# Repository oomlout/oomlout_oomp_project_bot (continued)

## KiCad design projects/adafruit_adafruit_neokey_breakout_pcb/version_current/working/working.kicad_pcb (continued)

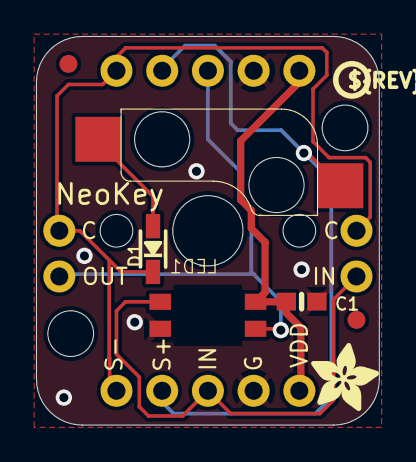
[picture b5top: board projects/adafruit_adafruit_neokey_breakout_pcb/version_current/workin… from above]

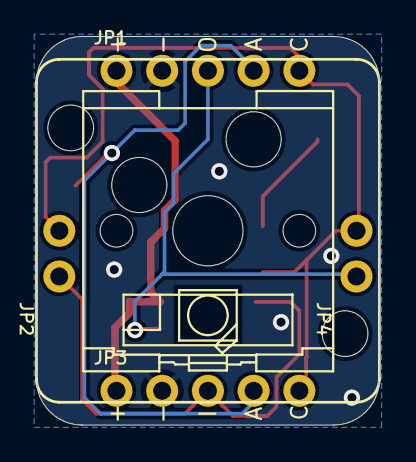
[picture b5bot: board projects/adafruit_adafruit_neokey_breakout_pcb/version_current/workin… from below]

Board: 2 copper layers, 19.1 x 21.6 mm, 14 parts (6 on the bottom side), 7 nets.

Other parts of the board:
@HOLE0, @HOLE1: (no value)
U$1: PCBFEAT-REV-040
U$2: ADAFRUIT_3.5MM

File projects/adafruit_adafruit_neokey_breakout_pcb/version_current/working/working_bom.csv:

Row,Description,Part,References,Value,Footprint,Quantity Per PCB,Status,Datasheet
1,,CAP_CERAMIC0603_NO,C1,1uF,0603-NO,1, ,
2,,DIODESOD-323,D1,1N4148,SOD-323,1, ,
3,,HEADER-1X2ROUND,JP2 JP4,HEADER-1X2ROUND,1X02_ROUND,2, ,
4,,HEADER-1X570MIL,JP1 JP3,HEADER-1X570MIL,1X05_ROUND_70,2, ,
5,,WS2812B_SK6812E,LED1,WS2812B_SK6812E,NEO3535_REVERSE,1, ,
6,,SWITCH_PUSHBUTTON_KAILH_SOCKET,SW1,SWITCH_PUSHBUTTON_KAILH_SOCKET,KAILH_SOCKET,1, ,





Project info:
Schematic:,working
Variant:,default
Revision:,
Date:,2023-08-03_17-21-22
KiCad Version:,7.0.6-7.0.6~ubuntu22.04.1
Statistics:
Component Groups:,6
Component Count:,8 (0 SMD/ 0 THT)
Fitted Components:,8 (0 SMD/ 0 THT)
Number of PCBs:,1
Total Components:,8

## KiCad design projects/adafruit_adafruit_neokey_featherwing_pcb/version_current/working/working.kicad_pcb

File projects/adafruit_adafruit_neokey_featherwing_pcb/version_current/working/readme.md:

# OOMP Project  
## Adafruit-NeoKey-FeatherWing-PCB  by adafruit  
  
oomp key: oomp_projects_flat_adafruit_adafruit_neokey_featherwing_pcb  
(snippet of original readme)  
  
-- Adafruit NeoKey FeatherWing PCB  
  
<a href="http://www.adafruit.com/products/4979"><br/>  
Click here to purchase one from the Adafruit shop</a>  
  
PCB files for the Adafruit NeoKey FeatherWing.   
  
Format is EagleCAD schematic and board layout  
* https://www.adafruit.com/product/4979  
  
--- Description  
  
The only thing better than a nice mechanical key, is two of them, and ones that also can glow any color of the rainbow - and that's what the Adafruit NeoKey FeatherWing will let you do! This Wing plugs into any/all Feather main boards and can fit two Cherry MX or compatible switches to turn your Feather into the lil'est macro keypad.  
  
Each Wing has two Kailh sockets, which means you can plug in any MX-compatible switches instead of soldering them in. You may need a little glue to keep the switches in place: hot glue or a dot of epoxy worked fine for us.  
  
Beneath each switch is a reverse-mount NeoPixel pointing up through the spot where many switches would have an LED to shine though. The two pixels are chained together so you can control them as one 2-pixel NeoPixel strand.  
  
We wired the switches up very simply, so you can use with any Feather. There's jumper pads you can cut to re-wire the switches and LED strand.  
  
* Switch A - Connects to the Feather pin to the left of SCL, on most Feathers this is pin D5  
* Switch B - Connects to the Feather pin two pins to the left of SCL, on most Feathers this is pin D6  
* NeoPixel Input - Connects  
  full source readme at [readme_src.md](readme_src.md)  
  
source repo at: [https://github.com/adafruit/Adafruit-NeoKey-FeatherWing-PCB](https://github.com/adafruit/Adafruit-NeoKey-FeatherWing-PCB)  
## Board  

## Schematic  

[schematic pdf](working_schematic.pdf)  
## Images

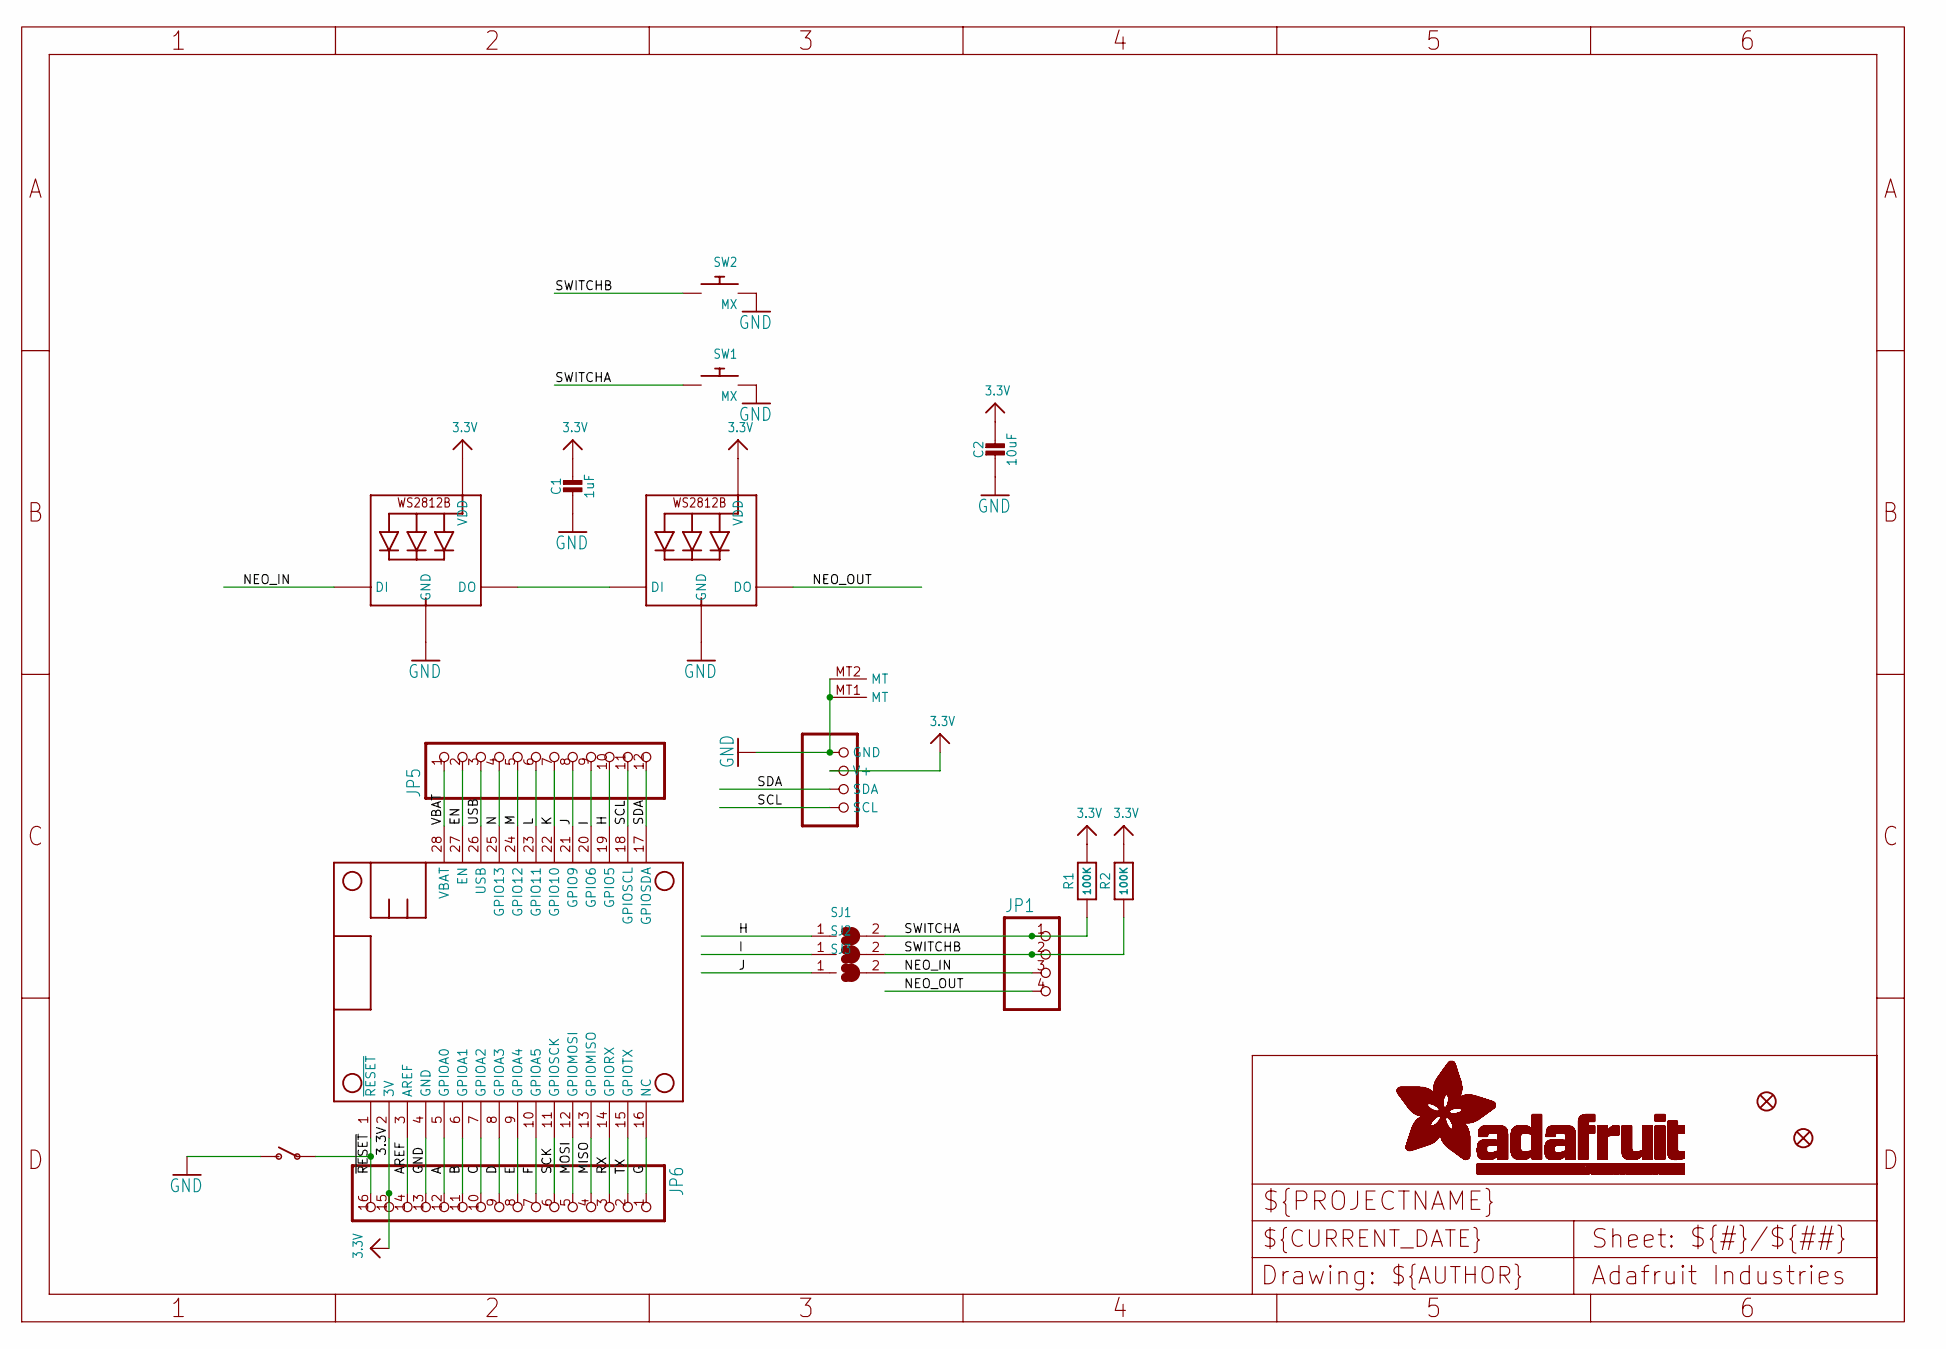
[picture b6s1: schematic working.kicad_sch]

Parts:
C1: 1uF; 0603-NO
C2: 10uF; 0805-NO
CONN1: STEMMA_I2C_QT; JST_SH4
FID1, FID2: FIDUCIAL_1MM
JP1: HEADER-1X4ROUND; 1X04_ROUND
JP5: HEADER-1X12; 1X12_ROUND
JP6: HEADER-1X16ROUND; 1X16_ROUND
LED1, LED2: WS2812B_SK6812E; NEO3535_REVERSE
MS1: FEATHERWING_NODIM
R1, R2: 100K; 0603-NO
SJ1, SJ2, SJ3: SOLDERJUMPERCLOSED; SOLDERJUMPER_CLOSEDWIRE
SW1, SW2: MX; KAILH_SOCKET
SW3: SWITCH_SPST_TACT_RA; SPST_TACTILE_RA

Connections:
3.3V: C1.1, C2.1, CONN1.2 (V+), JP6.15, LED1.1-VDD (VDD), LED2.1-VDD (VDD), MS1.2 (3V), R1.2, R2.2
A: JP6.12, MS1.5 (GPIOA0)
AREF: JP6.14, MS1.3 (AREF)
B: JP6.11, MS1.6 (GPIOA1)
C: JP6.10, MS1.7 (GPIOA2)
D: JP6.9, MS1.8 (GPIOA3)
E: JP6.8, MS1.9 (GPIOA4)
EN: JP5.2, MS1.27 (EN)
F: JP6.7, MS1.10 (GPIOA5)
G: JP6.1, MS1.16 (NC)
GND: C1.2, C2.2, CONN1.1 (GND), CONN1.MT1 (MT), CONN1.MT2 (MT), JP6.13, LED1.3-GND (GND), LED2.3-GND (GND), MS1.4 (GND), SW1.1, SW2.1, SW3.2 (S)
H: JP5.10, MS1.19 (GPIO5), SJ1.1
I: JP5.9, MS1.20 (GPIO6), SJ2.1
J: JP5.8, MS1.21 (GPIO9), SJ3.1
K: JP5.7, MS1.22 (GPIO10)
L: JP5.6, MS1.23 (GPIO11)
M: JP5.5, MS1.24 (GPIO12)
MISO: JP6.4, MS1.13 (GPIOMISO)
MOSI: JP6.5, MS1.12 (GPIOMOSI)
N: JP5.4, MS1.25 (GPIO13)
unnamed: LED1.4-DIN (DI), LED2.2-DOUT (DO)
NEO_IN: JP1.3, LED2.4-DIN (DI), SJ3.2
NEO_OUT: JP1.4, LED1.2-DOUT (DO)
RX: JP6.3, MS1.14 (GPIORX)
SCK: JP6.6, MS1.11 (GPIOSCK)
SCL: CONN1.4 (SCL), JP5.11, MS1.18 (GPIOSCL)
SDA: CONN1.3 (SDA), JP5.12, MS1.17 (GPIOSDA)
SWITCHA: JP1.1, R1.1, SJ1.2, SW1.2
SWITCHB: JP1.2, R2.1, SJ2.2, SW2.2
TX: JP6.2, MS1.15 (GPIOTX)
USB: JP5.3, MS1.26 (USB)
VBAT: JP5.1, MS1.28 (VBAT)
~RESET: JP6.16, MS1.1 (~RESET), SW3.1

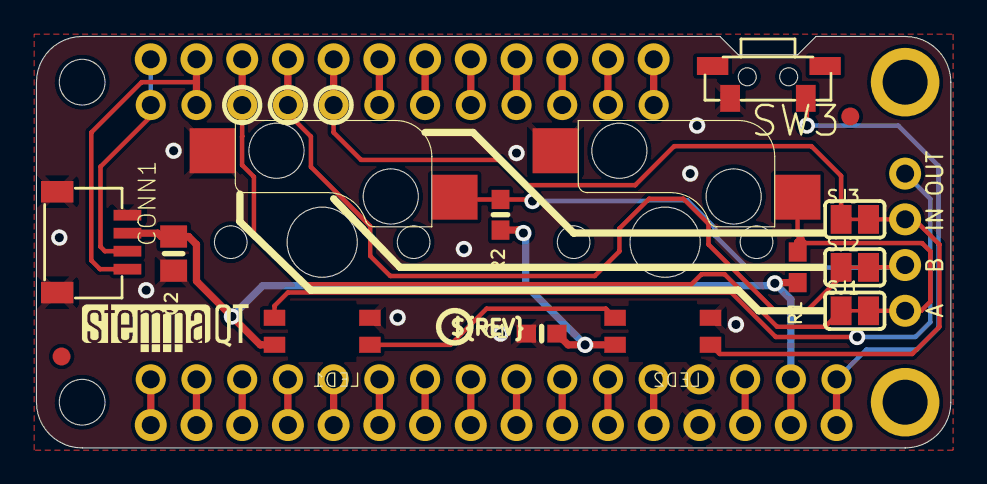
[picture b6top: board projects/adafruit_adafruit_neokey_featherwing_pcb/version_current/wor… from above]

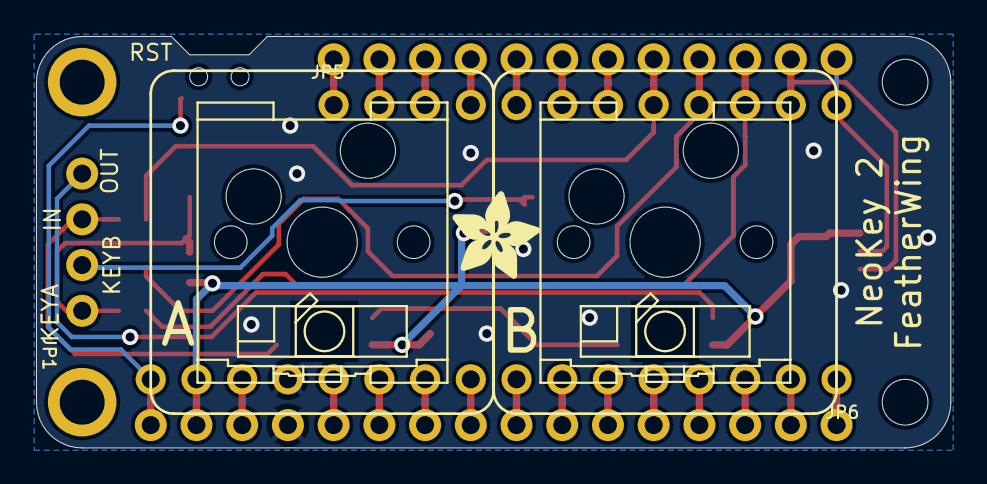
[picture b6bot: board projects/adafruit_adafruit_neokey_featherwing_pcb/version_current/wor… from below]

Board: 2 copper layers, 50.8 x 22.9 mm, 22 parts (9 on the bottom side), 33 nets.

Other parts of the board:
U$7: ADAFRUIT_5MM
U$8: PCBFEAT-REV-040
U$11: STEMMAQT
